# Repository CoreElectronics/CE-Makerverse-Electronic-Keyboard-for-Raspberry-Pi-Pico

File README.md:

# Makerverse™ Electronic Keyboard for Raspberry Pi Pico

This is the repo for the Core Electronics [Makerverse Electronic Keyboard for Raspberry Pi Pico](https://core-electronics.com.au/catalog/product/view/sku/ce08494).

The PCB layout project requires KiCAD 6.0 or newer to view. The schematic is provided in PDF format in the Documents folder.

## License
This project is open source - please review the LICENSE.md file for further licensing information.

If you have any technical questions, or concerns about licensing, please contact technical support on the [Core Electronics forums](https://forum.core-electronics.com.au/).

*\"PiicoDev\" and the PiicoDev logo are trademarks of Core Electronics Pty Ltd.*

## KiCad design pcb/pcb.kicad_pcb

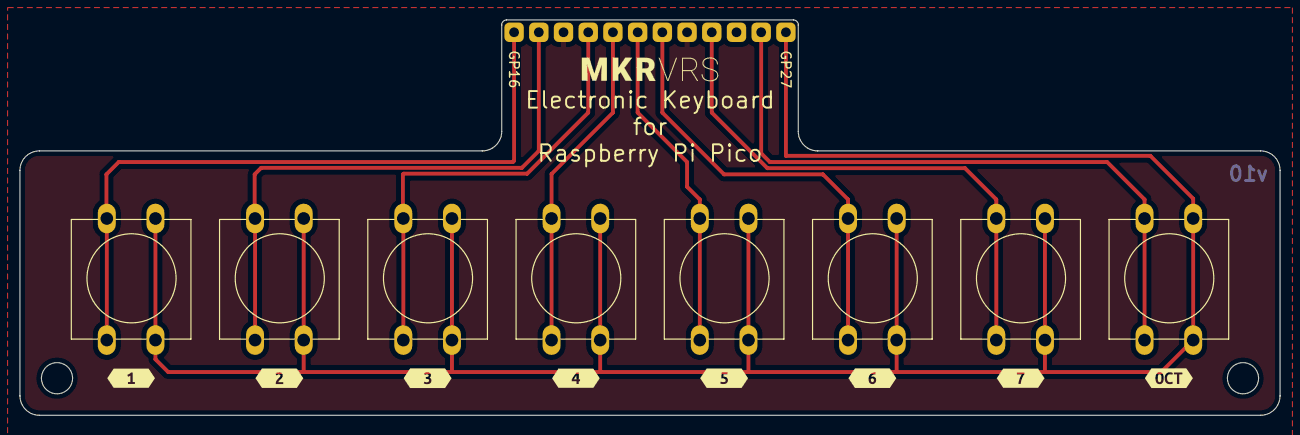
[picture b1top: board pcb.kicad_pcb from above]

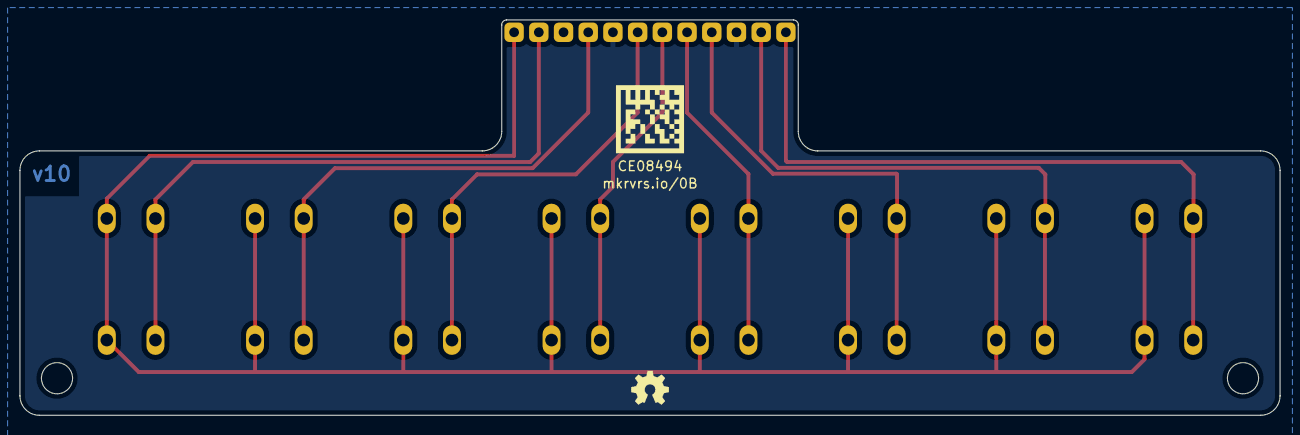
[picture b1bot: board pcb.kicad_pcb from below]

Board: 2 copper layers, 129.5 x 40.6 mm, 22 parts (2 on the bottom side), 10 nets.

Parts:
G1: Label_PCB_Art; CE08494
G2: LOGO_Makerverse; makerverse_logo_short_14.0x2.4mm
H1, H2: MountingHole; MountingHole_3.2mm_M3
J1: Conn_01x12; PinHeader_1x12_P2.54mm_Vertical
LOGO1: Logo_Open_Hardware_Small; oshw_3.9x3.5mm
SW1, SW2, SW3, SW4, SW5, SW6, SW7, SW8: SW_Push; SW_PUSH-12mm
kibuzzard-6257AAD7: G***; kibuzzard-6257AAD7
kibuzzard-6257AADC: G***; kibuzzard-6257AADC
kibuzzard-6257AAE6: G***; kibuzzard-6257AAE6
kibuzzard-6257AAEB: G***; kibuzzard-6257AAEB
kibuzzard-6257AAF1: G***; kibuzzard-6257AAF1
kibuzzard-6257AB2E: G***; kibuzzard-6257AB2E
kibuzzard-6257AB3B: G***; kibuzzard-6257AB3B
kibuzzard-6257AB37: G***; kibuzzard-6257AB37

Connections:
GND: J1.5, J1.10
unnamed: J1.2, SW1.1
unnamed: J1.4, SW2.1
unnamed: J1.6, SW3.1
unnamed: J1.7, SW4.1
unnamed: J1.8, SW5.1
unnamed: J1.9, SW6.1
unnamed: J1.11, SW7.1
unnamed: J1.12, SW8.1
VCC: J1.1, SW1.2, SW2.2, SW3.2, SW4.2, SW5.2, SW6.2, SW7.2, SW8.2
